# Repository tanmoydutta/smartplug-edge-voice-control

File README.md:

# A Module to hack a smart plug with Voice control, using Voice Recognition with Edge Analytics
Orthosie is a NINA-B306 powered Smart Plug controller module. The module contains basic circuitry for interfacing and programming and a PDM microphone for Speech recognition. 

This is a replacement / hacking module for modern smart plugs using ESP02S or CB2S modules from Tuya.

The diagram below shows the pinout of the module including programming and debug contact interfaces (USB Serial and Software Debug)

The contact interfaces (SWD and USB) can be connected to programming interface and devices using Pogo pin connectors with the help of suitable clips as shown below in the image.

The purpose of this module is to add a 'voice recognition on edge' capability to a Smart Plug. The NINA module also provides BLE capability and makes communication and control via BLE also possible.

This is an Open Source Hardware certified by OSHWA - 

<p align="center">
  
</p>

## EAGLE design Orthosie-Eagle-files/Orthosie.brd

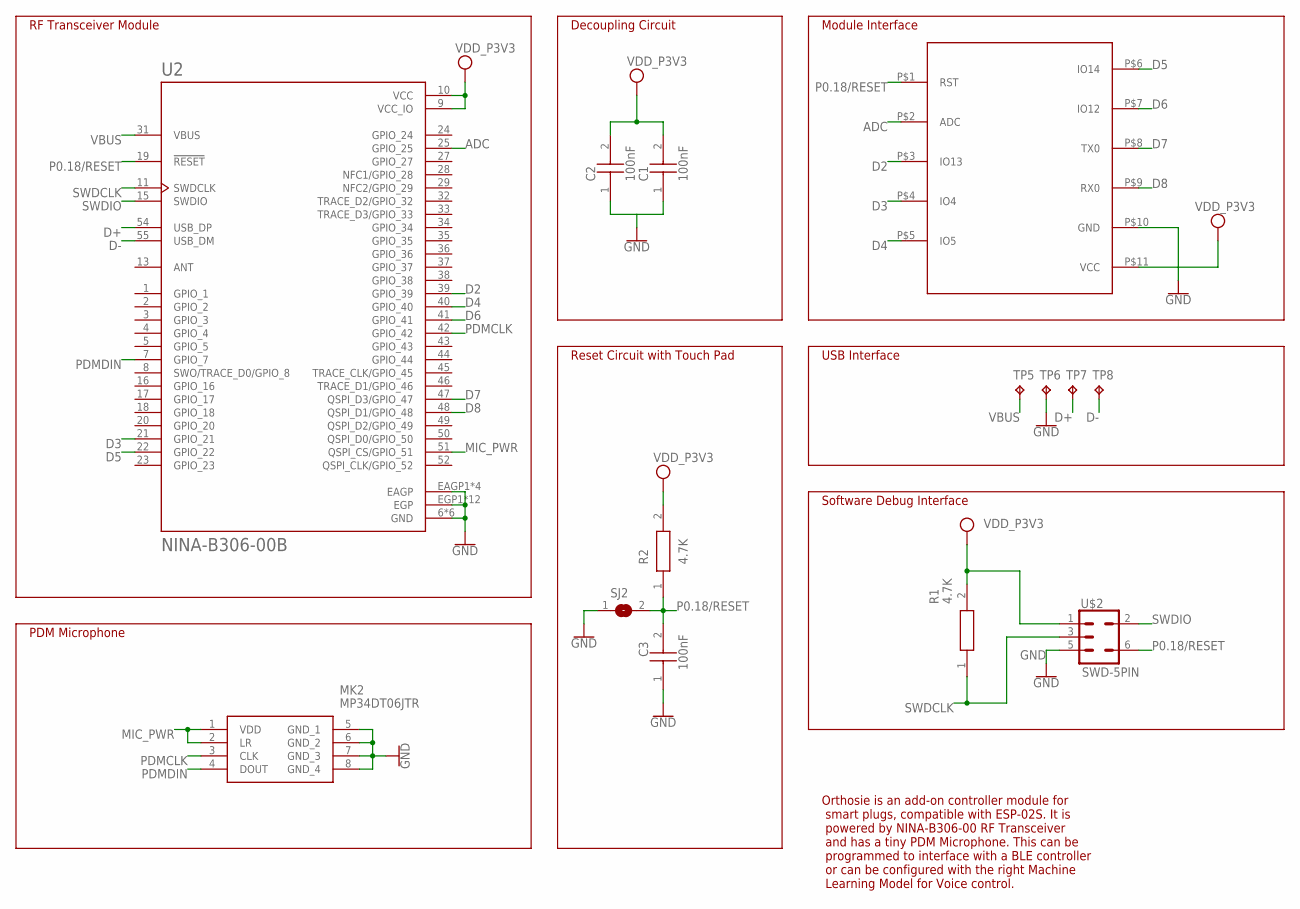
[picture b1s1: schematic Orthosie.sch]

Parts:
C1, C2, C3: 100nF; CAPC1005X55N
MK2: MP34DT06JTR
R1, R2: 4.7K; RESC1005X40N
SJ2: SJ
TP5, TP6, TP7, TP8: TPB1,27; B1,27
U2: NINA-B306-00B; XCVR_NINA-B306-00B
U$1: ESP02SESP02S_MIRROR; ESP02S_MIRROR
U$2: SWD-5PIN; PAD_05_03X2_TP_NO4

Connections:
ADC: U2.25 (GPIO_25), U$1.P$2 (ADC)
D2: U2.39 (GPIO_39), U$1.P$3 (IO13)
D3: U2.21 (GPIO_21), U$1.P$4 (IO4)
D4: U2.40 (GPIO_40), U$1.P$5 (IO5)
D5: U2.22 (GPIO_22), U$1.P$6 (IO14)
D6: U2.41 (GPIO_41), U$1.P$7 (IO12)
D7: U2.47 (QSPI_D3/GPIO_47), U$1.P$8 (TX0)
D8: U2.48 (QSPI_D1/GPIO_48), U$1.P$9 (RX0)
D+: TP7.TP, U2.54 (USB_DP)
D-: TP8.TP, U2.55 (USB_DM)
GND: C1.1, C2.1, C3.1, MK2.5 (GND_1), MK2.6 (GND_2), MK2.7 (GND_3), MK2.8 (GND_4), SJ2.1, TP6.TP, U2.6 (GND), U2.12 (GND), U2.14 (GND), U2.26 (GND), U2.30 (GND), U2.53 (GND), U2.EAGP1 (EAGP), U2.EAGP2 (EAGP), U2.EAGP3 (EAGP), U2.EAGP4 (EAGP), U2.EGP1 (EGP), U2.EGP2 (EGP), U2.EGP3 (EGP), U2.EGP4 (EGP), U2.EGP5 (EGP), U2.EGP6 (EGP), U2.EGP7 (EGP), U2.EGP8 (EGP), U2.EGP9 (EGP), U2.EGP10 (EGP), U2.EGP11 (EGP), U2.EGP12 (EGP), U$1.P$10 (GND), U$2.5
MIC_PWR: MK2.1 (VDD), MK2.2 (LR), U2.51 (QSPI_CS/GPIO_51)
P0.18/RESET: C3.2, R2.1, SJ2.2, U2.19 (!RESET), U$1.P$1 (RST), U$2.6
PDMCLK: MK2.3 (CLK), U2.42 (GPIO_42)
PDMDIN: MK2.4 (DOUT), U2.7 (GPIO_7)
SWDCLK: R1.1, U2.11 (SWDCLK), U$2.3
SWDIO: U2.15 (SWDIO), U$2.2
VBUS: TP5.TP, U2.31 (VBUS)
VCC: C1.2, C2.2, R1.2, R2.2, U2.9 (VCC_IO), U2.10 (VCC), U$1.P$11 (VCC), U$2.1

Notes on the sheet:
PDM Microphone
RF Transceiver Module
Decoupling Circuit
Reset Circuit with Touch Pad
Module Interface
USB Interface
Software Debug Interface
Orthosie is an add-on controller module for smart plugs, compatible with ESP-02S. It is powered by NINA-B306-00 RF Transceiver and has a tiny PDM Microphone. This can be programmed to interface with a BLE controller or can be configured with the right Machine Learning Model for Voice control.

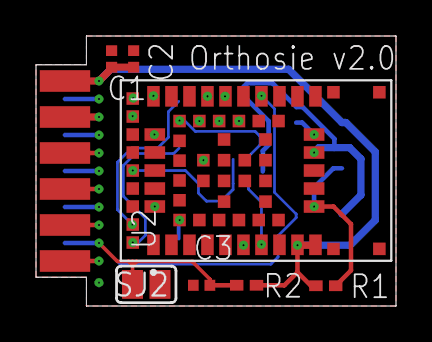
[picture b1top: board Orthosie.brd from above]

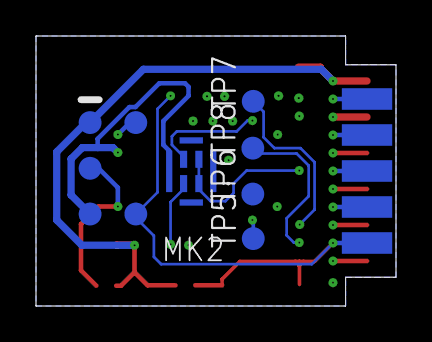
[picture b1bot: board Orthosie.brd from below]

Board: 6 copper layers, 20.0 x 15.0 mm, 14 parts (6 on the bottom side), 19 nets.

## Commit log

2024-03-15 Update README.md
    Updating the heading
2024-03-24 Adding Eagle files
2024-03-24 Update README.md
    Initial description and pictures.
2024-03-24 Adding smart plug hack image
2024-03-24 Update README.md
    Smart Plug hack image added
2024-03-25 Pinout added
2024-03-25 Update README.md
    Documentation update with images for pinout
2024-03-25 Added installed Orthosie module on Smart plug pic
2024-03-25 Added installed cb2s moodule on Smart plug pic
2024-03-25 Update README.md
    Updating the installed module image
2024-03-25 Update README.md
    Testing image
2024-03-25 Update README.md
    Corrected image path
2024-03-25 pogo connector image added
2024-03-25 Update README.md
    Added image for the pogo connector
2024-03-25 Pin Correction
2024-03-25 Update README.md
    Update documentation
2024-03-25 Update README.md
    Update pinout documentation
2024-04-10 Adding OSHWA mark
2024-04-10 Update README.md
    Adding OSHWA Mark
2024-04-11 New images
2024-04-11 Image updated
2024-04-11 Update README.md
    Updated
2024-04-12 Image update
2024-04-12 Update README.md
    Update OSHWA link

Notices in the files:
parts and their libraries:
SparkFun-Connectors: Licensing: Creative Commons ShareAlike 4.0 International - https://creativecommons.org/licenses/by-sa/4.0
